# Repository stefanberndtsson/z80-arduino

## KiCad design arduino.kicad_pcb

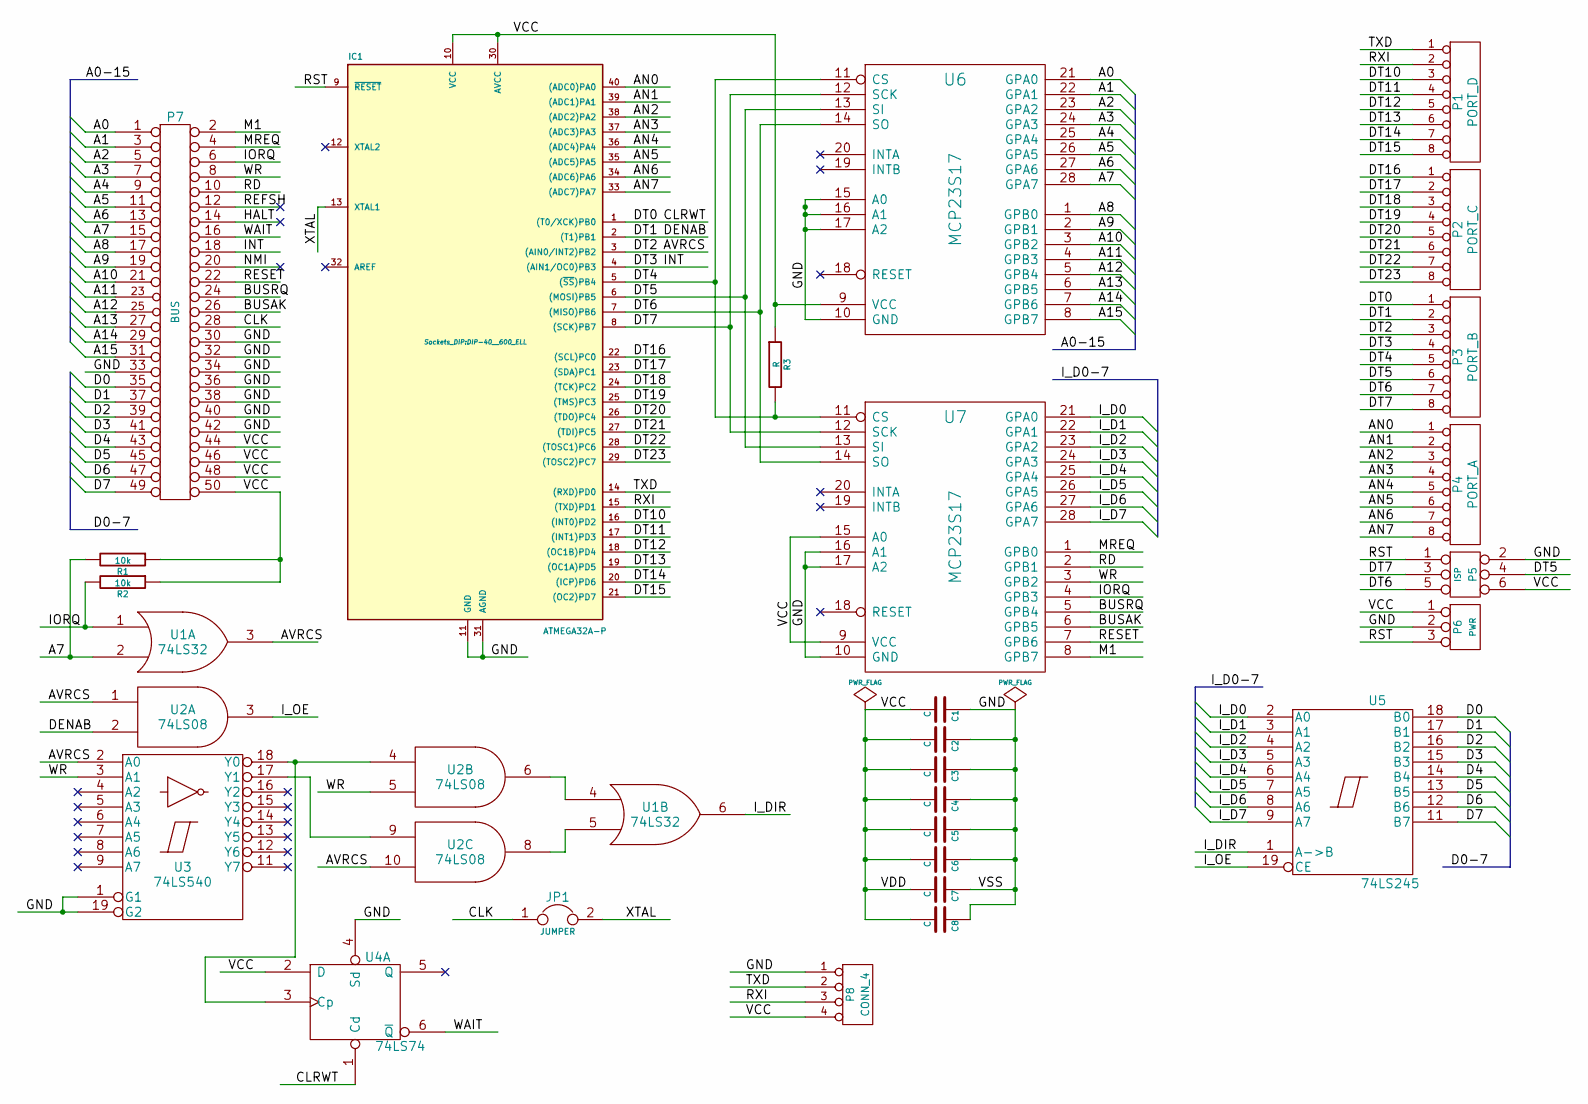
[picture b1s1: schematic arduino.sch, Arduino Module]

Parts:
C1, C2, C3, C4, C5, C6, C7, C8: C; Capacitor3MMDiscRM2.5
IC1: ATMEGA32A-P; DIP-40__600_ELL
JP1: JUMPER; Socket_Strip_Straight_1x02
P1: PORT_D; Socket_Strip_Straight_1x08
P2: PORT_C; Socket_Strip_Straight_1x08
P3: PORT_B; Socket_Strip_Straight_1x08
P4: PORT_A; Socket_Strip_Straight_1x08
P5: ISP; Socket_Strip_Straight_2x03
P6: PWR; Socket_Strip_Straight_1x03
P7: BUS; Socket_Strip_Straight_2x25
P8: CONN_4; Socket_Strip_Straight_1x04
R1, R2: 10k; Resistor_Horizontal_RM10mm
R3: R; Resistor_Horizontal_RM10mm
U1: 74LS32; DIP-14__300_ELL
U2: 74LS08; DIP-14__300_ELL
U3: 74LS540; DIP-20__300_ELL
U4: 74LS74; DIP-14__300_ELL
U5: 74LS245; DIP-20__300_ELL
U6, U7: MCP23S17; DIP-28__300_ELL

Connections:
/A0: P7.1, U6.21 (GPA0)
/A1: P7.3, U6.22 (GPA1)
/A2: P7.5, U6.23 (GPA2)
/A3: P7.7, U6.24 (GPA3)
/A4: P7.9, U6.25 (GPA4)
/A5: P7.11, U6.26 (GPA5)
/A6: P7.13, U6.27 (GPA6)
/A7: P7.15, R1.2, U1.2, U6.28 (GPA7)
/A8: P7.17, U6.1 (GPB0)
/A9: P7.19, U6.2 (GPB1)
/A10: P7.21, U6.3 (GPB2)
/A11: P7.23, U6.4 (GPB3)
/A12: P7.25, U6.5 (GPB4)
/A13: P7.27, U6.6 (GPB5)
/A14: P7.29, U6.7 (GPB6)
/A15: P7.31, U6.8 (GPB7)
/AN0: IC1.40 ((ADC0)PA0), P4.1
/AN1: IC1.39 ((ADC1)PA1), P4.2
/AN2: IC1.38 ((ADC2)PA2), P4.3
/AN3: IC1.37 ((ADC3)PA3), P4.4
/AN4: IC1.36 ((ADC4)PA4), P4.5
/AN5: IC1.35 ((ADC5)PA5), P4.6
/AN6: IC1.34 ((ADC6)PA6), P4.7
/AN7: IC1.33 ((ADC7)PA7), P4.8
/AVRCS: IC1.3 ((AIN0/INT2)PB2), P3.3, U1.3, U2.1, U2.10, U3.2 (A0)
/BUSAK: P7.26, U7.6 (GPB5)
/BUSRQ: P7.24, U7.5 (GPB4)
/CLK: JP1.1, P7.28
/CLRWT: IC1.1 ((T0/XCK)PB0), P3.1, U4.1 (Cd)
/D0: P7.35, U5.18 (B0)
/D1: P7.37, U5.17 (B1)
/D2: P7.39, U5.16 (B2)
/D3: P7.41, U5.15 (B3)
/D4: P7.43, U5.14 (B4)
/D5: P7.45, U5.13 (B5)
/D6: P7.47, U5.12 (B6)
/D7: P7.49, U5.11 (B7)
/DENAB: IC1.2 ((T1)PB1), P3.2, U2.2
/DT3: IC1.4 ((AIN1/OC0)PB3), P3.4, P7.18
/DT4: IC1.5 ((~SS~)PB4), P3.5, R3.2, U6.11 (CS), U7.11 (CS)
/DT5: IC1.6 ((MOSI)PB5), P3.6, P5.4, U6.13 (SI), U7.13 (SI)
/DT6: IC1.7 ((MISO)PB6), P3.7, P5.5, U6.14 (SO), U7.14 (SO)
/DT7: IC1.8 ((SCK)PB7), P3.8, P5.3, U6.12 (SCK), U7.12 (SCK)
/DT10: IC1.16 ((INT0)PD2), P1.3
/DT11: IC1.17 ((INT1)PD3), P1.4
/DT12: IC1.18 ((OC1B)PD4), P1.5
/DT13: IC1.19 ((OC1A)PD5), P1.6
/DT14: IC1.20 ((ICP)PD6), P1.7
/DT15: IC1.21 ((OC2)PD7), P1.8
/DT16: IC1.22 ((SCL)PC0), P2.1
/DT17: IC1.23 ((SDA)PC1), P2.2
/DT18: IC1.24 ((TCK)PC2), P2.3
/DT19: IC1.25 ((TMS)PC3), P2.4
/DT20: IC1.26 ((TDO)PC4), P2.5
/DT21: IC1.27 ((TDI)PC5), P2.6
/DT22: IC1.28 ((TOSC1)PC6), P2.7
/DT23: IC1.29 ((TOSC2)PC7), P2.8
/HALT: P7.14
/IORQ: P7.6, R2.2, U1.1, U7.4 (GPB3)
/I_D0: U5.2 (A0), U7.21 (GPA0)
/I_D1: U5.3 (A1), U7.22 (GPA1)
/I_D2: U5.4 (A2), U7.23 (GPA2)
/I_D3: U5.5 (A3), U7.24 (GPA3)
/I_D4: U5.6 (A4), U7.25 (GPA4)
/I_D5: U5.7 (A5), U7.26 (GPA5)
/I_D6: U5.8 (A6), U7.27 (GPA6)
/I_D7: U5.9 (A7), U7.28 (GPA7)
/I_DIR: U1.6, U5.1 (A->B)
/I_OE: U2.3, U5.19 (CE)
/M1: P7.2, U7.8 (GPB7)
/MREQ: P7.4, U7.1 (GPB0)
/NMI: P7.20
/RD: P7.10, U7.2 (GPB1)
/REFSH: P7.12
/RESET: P7.22, U7.7 (GPB6)
/RST: IC1.9 (~RESET), P5.1, P6.3
/RXI: IC1.15 ((TXD)PD1), P1.2, P8.3
/TXD: IC1.14 ((RXD)PD0), P1.1, P8.2
/WAIT: P7.16, U4.6 (~Q)
/WR: P7.8, U2.5, U3.3 (A1), U7.3 (GPB2)
/XTAL: IC1.13 (XTAL1), JP1.2
GND: C1.1, C2.1, C3.1, C4.1, C5.1, C6.1, C7.1, C8.1, IC1.11 (GND), IC1.31 (AGND), P5.2, P6.2 (PM), P7.30, P7.32, P7.33, P7.34, P7.36, P7.38, P7.40, P7.42, P8.1, U1.7 (GND), U2.7 (GND), U3.1 (G1), U3.10 (GND), U3.19 (G2), U4.4 (Sd), U4.7 (GND), U5.10 (GND), U6.10 (GND), U6.15 (A0), U6.16 (A1), U6.17 (A2), U7.10 (GND), U7.16 (A1), U7.17 (A2)
unnamed: U1.4, U2.6
unnamed: U1.5, U2.8
unnamed: U2.4, U3.18 (Y0), U4.3 (Cp)
unnamed: U2.9, U3.17 (Y1)
VCC: C1.2, C2.2, C3.2, C4.2, C5.2, C6.2, C7.2, C8.2, IC1.10 (VCC), IC1.30 (AVCC), P5.6, P6.1, P7.44, P7.46, P7.48, P7.50, P8.4, R1.1, R2.1, R3.1, U1.14 (VCC), U2.14 (VCC), U3.20 (VCC), U4.2 (D), U4.14 (VCC), U5.20 (VCC), U6.9 (VCC), U7.9 (VCC), U7.15 (A0)

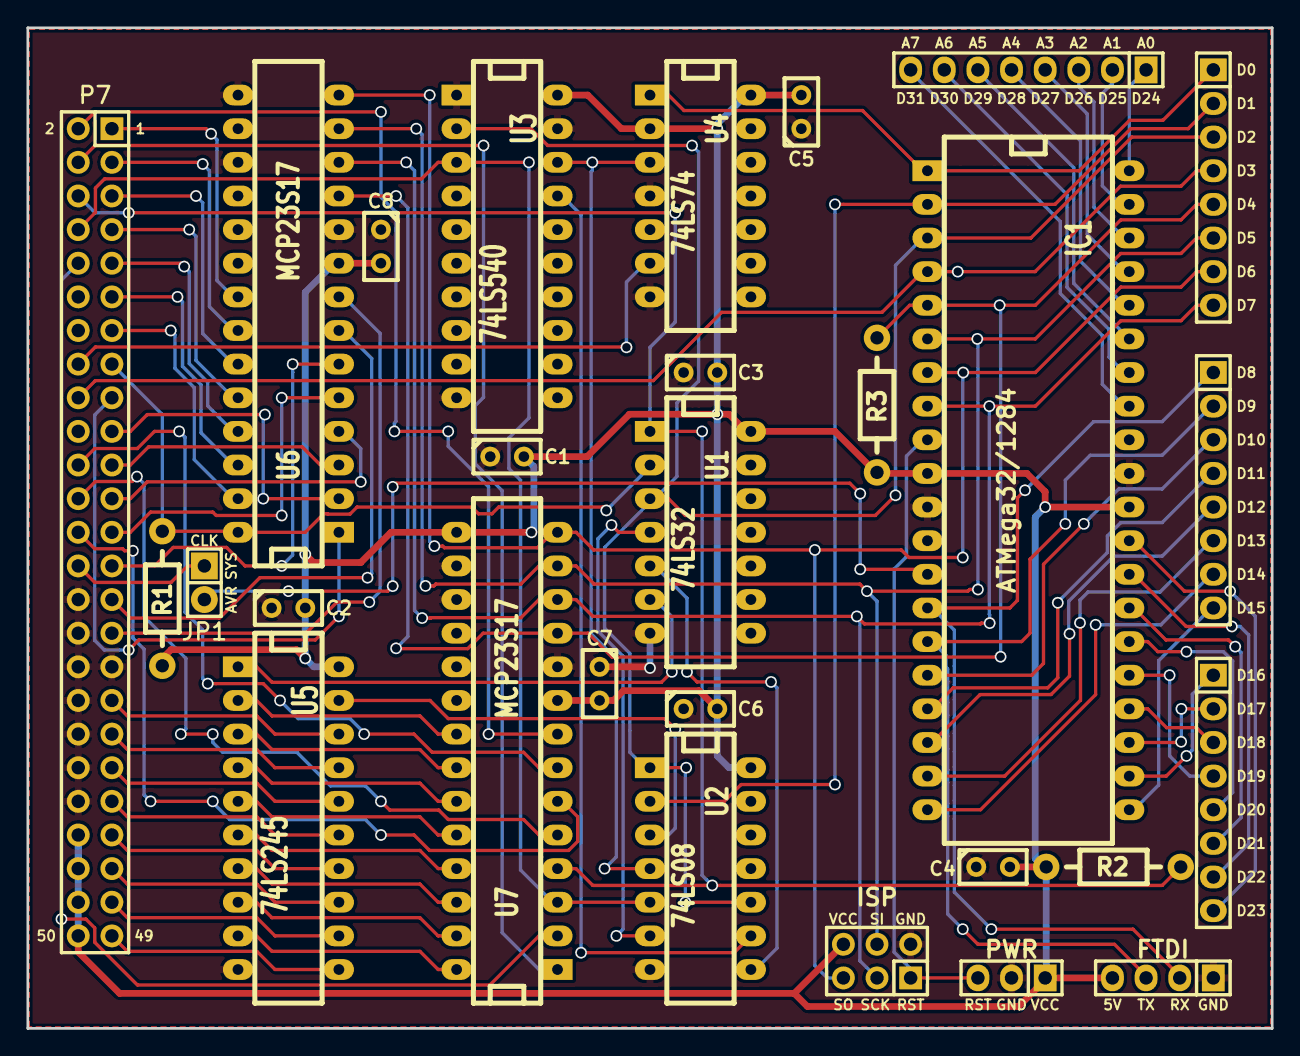
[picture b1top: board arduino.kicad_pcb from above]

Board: 2 copper layers, 94.0 x 75.6 mm, 28 parts (0 on the bottom side), 84 nets.

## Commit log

2014-08-15 Initial
2014-08-15 Replace Arduino Pro Mini Clone with an ATMega32A instead
2014-08-15 Some changes to fill zones better
2014-08-17 Silkscreen texts and a jumper to select system clock or feed a separate one for the AVR
2014-08-30 Some silkscreen updates
2014-08-31 Fix a bug and add an FTDI connector
2014-08-31 Fix error with ISP port, and move data bus control from PortA to free that one up
2014-09-04 Move some pins from AVR to one of the MCP:s to free up PORT A, C and D
